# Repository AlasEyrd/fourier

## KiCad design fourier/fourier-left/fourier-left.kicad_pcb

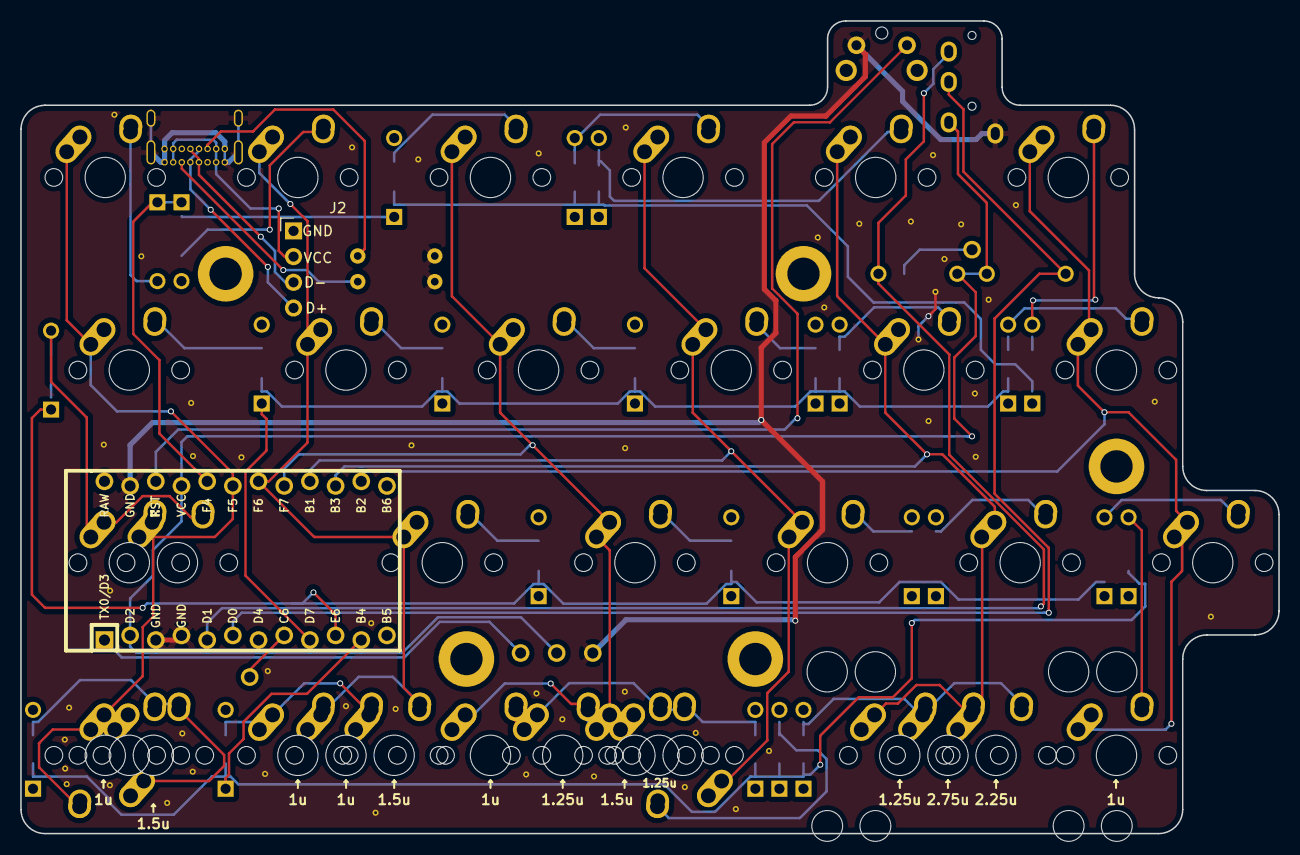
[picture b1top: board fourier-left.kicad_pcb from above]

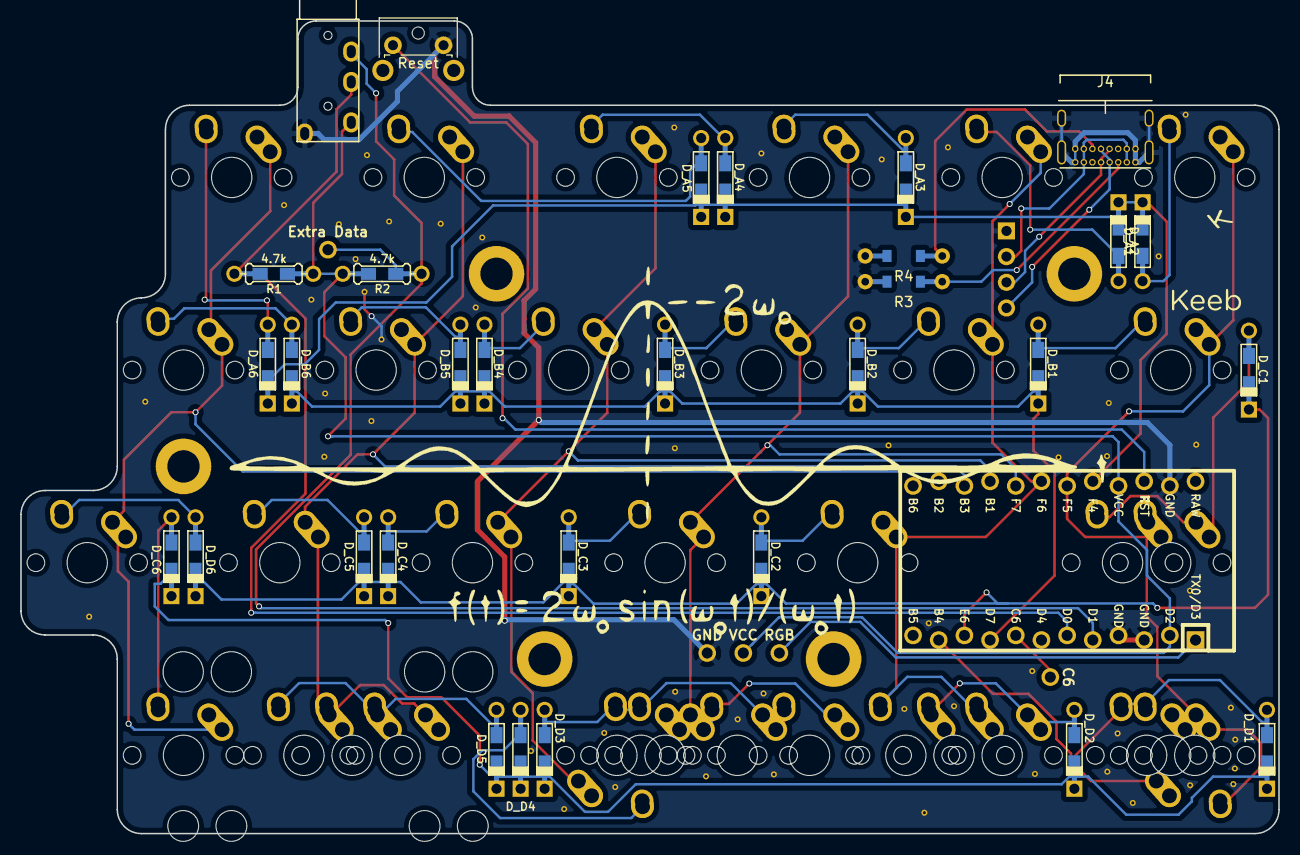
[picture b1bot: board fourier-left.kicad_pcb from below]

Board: 2 copper layers, 124.4 x 80.4 mm, 72 parts (8 on the bottom side), 27 nets.

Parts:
D_A1, D_A2, D_A3, D_A4, D_A5, D_A6: D; Diode-Hybrid-Back
D_B1, D_B2, D_B3, D_B4, D_B5, D_B6: D; Diode-Hybrid-Back
D_C1, D_C2, D_C3, D_C4, D_C5, D_C6: D; Diode-Hybrid-Back
D_D1, D_D2, D_D3, D_D4, D_D5, D_D6: D; Diode-Hybrid-Back
J1: VCC; Single-Pad
J2: Conn_01x04_Female; PinHeader_1x04_P2.54mm_Horizontal
J3: RGB; Single-Pad
J4: USB_C_Receptacle_USB2.0; USB_C_GCT_USB4085
J6: C6; Single-Pad
J7: GND; Single-Pad
R1, R2: 4.7k; Resistor-Hybrid-Back
R3, R4: 5.1k; ComboResistor
SW_A1, SW_A2, SW_A3, SW_A4, SW_A5, SW_A6: SW_PUSH; MX-1U-NoLED
SW_B1: SW_PUSH; MX-1.25U-NoLED
SW_B2, SW_B3, SW_B4, SW_B5, SW_B6: SW_PUSH; MX-1U-NoLED
SW_C1: SW_PUSH; MX-1.75U-NoLED
SW_C2, SW_C3, SW_C4, SW_C5, SW_C6: SW_PUSH; MX-1U-NoLED
SW_Cb1: SW_PUSH; MX-1.25U-NoLED
SW_D1, SW_D3: SW_PUSH; MX-1.25U-NoLED
SW_D2, SW_D4, SW_D6: SW_PUSH; MX-1U-NoLED
SW_D5: SW_PUSH; MX-2.75U-ReversedStabilizers-NoLED
SW_Db1, SW_Db2: SW_PUSH; MX-1.5U-NoLED
SW_Db3: SW_PUSH; MX-1.25U-NoLED
SW_Db5: SW_PUSH; MX-2.25U-ReversedStabilizers-NoLED
SW_Dc1, SW_Dc2: SW_PUSH; MX-1U-NoLED
SW_Dc3: SW_PUSH; MX-1.5U-NoLED
SW_Dc5: SW_PUSH; MX-1.25U-NoLED
SW_Dd3: SW_PUSH; MX-1U-NoLED
SW_RST1: Reset; SW_Tactile_SPST_Angled_MJTP1117
U1: ProMicro; ArduinoProMicro-ZigZag
U2: TRRS; TRRS-PJ-320A
W2: Extra Data; Single-Pad

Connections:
C6: J6.1, U1.8
GND: J2.1, J4.A1, J4.A12, J4.B1, J4.B12, J4.S1, J7.1, R3.1, R4.1, SW_RST1.2, U1.3, U1.4, U1.23, U2.1
unnamed: SW_C1.2, SW_Cb1.1
unnamed: SW_D1.2, SW_Db1.2, SW_Dc1.1
unnamed: SW_D2.2, SW_Db2.1, SW_Dc2.1
unnamed: SW_D5.1, SW_Db5.2, SW_Dc5.2
unnamed: J2.2, J4.A4, J4.A9, J4.B4, J4.B9
unnamed: J2.3, J4.A7, J4.B7
unnamed: J2.4, J4.A6, J4.B6
unnamed: J4.A5, R3.2
unnamed: J4.B5, R4.2
unnamed: SW_D3.1, SW_Db3.2, SW_Dc3.2, SW_Dd3.2
RGB: J3.1, U1.1
VCC: J1.1, R1.2, R2.1, U1.2, U1.21, U2.2
col1: SW_A1.1, SW_B1.1, SW_C1.1, SW_Cb1.2, SW_D1.1, SW_Db1.1, SW_Dc1.2, U1.19
col2: SW_A2.1, SW_B2.1, SW_C2.1, SW_D2.1, SW_Db2.2, SW_Dc2.2, U1.18
col3: SW_A3.1, SW_B3.1, SW_C3.1, SW_D3.2, SW_Db3.1, SW_Dc3.1, SW_Dd3.1, U1.17
col4: SW_A4.1, SW_B4.1, SW_C4.1, SW_D4.1, U1.16
col5: SW_A5.1, SW_B5.1, SW_C5.1, SW_D5.2, SW_Db5.1, SW_Dc5.1, U1.15
col6: SW_A6.1, SW_B6.1, SW_C6.1, SW_D6.1, U1.14
data: R1.1, U1.6, U2.3
data2: R2.2, U1.5, U2.4, W2.1
reset: SW_RST1.1, U1.22
rowA: D_A1.1, D_A2.1, D_A3.1, D_A4.1, D_A5.1, D_A6.1, U1.20
rowB: D_B1.1, D_B2.1, D_B3.1, D_B4.1, D_B5.1, D_B6.1, U1.9
rowC: D_C1.1, D_C2.1, D_C3.1, D_C4.1, D_C5.1, D_C6.1, U1.10
rowD: D_D1.1, D_D2.1, D_D3.1, D_D4.1, D_D5.1, D_D6.1, U1.11

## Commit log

2020-05-23 Alas v1
    moved pro micro location and added a USB C port for pigtail cables
